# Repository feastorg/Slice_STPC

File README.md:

# Slice STPC

## Introduction

Stepper motor controller Slice for BREADS-compatible systems.
This Slice is a carrier board for the [Stepper_card](https://github.com/IanVDS/stepper_card) board. It can carry up to four stepper cards, each with a DRV8825 stepper driver with microstepping and SPI pins for encoder reading.

## Usage

[Explain how to use the project. Include examples and screenshots if applicable.]

## Documentation

Please refer to the [docs](/docs) for more info.

---

<div align="center">
  
</div>

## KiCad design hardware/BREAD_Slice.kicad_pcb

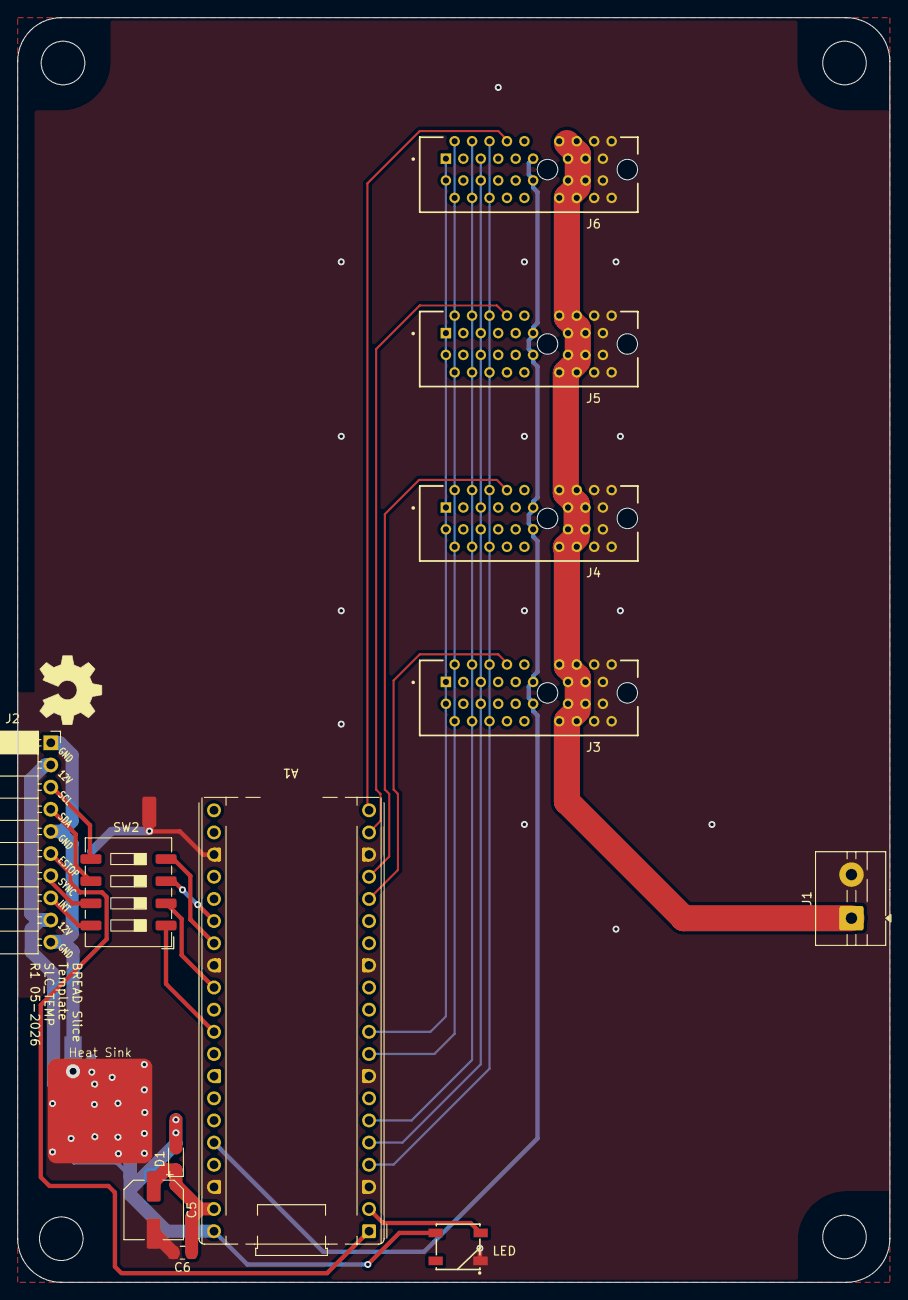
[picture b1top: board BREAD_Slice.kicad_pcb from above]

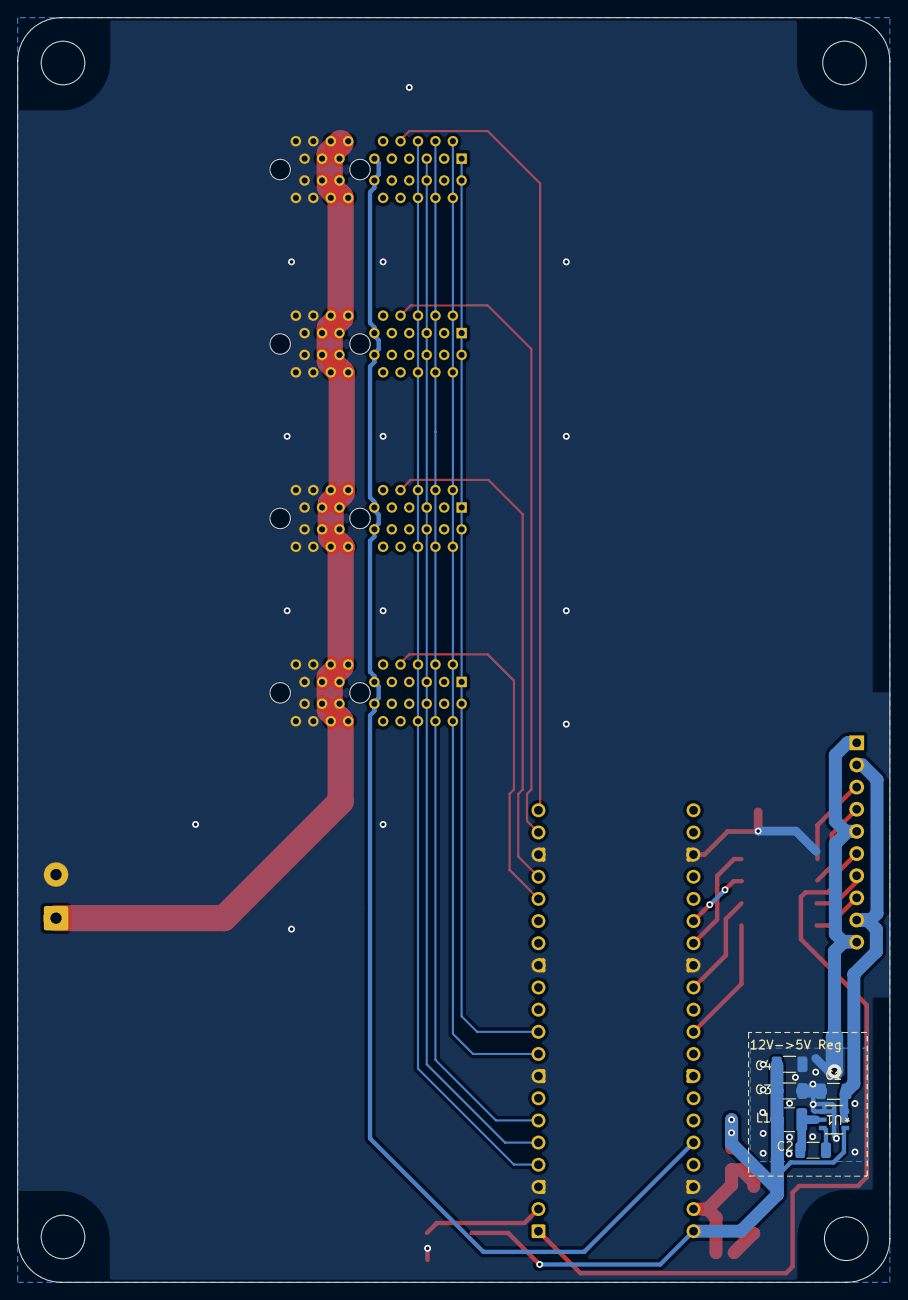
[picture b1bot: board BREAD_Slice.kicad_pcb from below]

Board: 4 copper layers, 100.0 x 145.0 mm, 25 parts (7 on the bottom side), 37 nets.

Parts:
A1: RaspberryPi_Pico; RaspberryPi_Pico_THT
C1: 10u; C_1206_3216Metric
C2: 100nF; C_1206_3216Metric
C3, C4: 22uF; C_1206_3216Metric
C5: 47u 25V; CP_Elec_6.3x7.7
C6: 0.1u; C_0805_2012Metric_Pad1.18x1.45mm_HandSolder
D1: BAT54WS-7-F; D_SOD-323_HandSoldering
D2: WS2812B_5050; WS2812-5050-4PIN
H1, H2, H3, H4: MountingHole; MountingHole_5mm
HS1: Heatsink_Pad; Thermal_Pad
J1: Screw_Terminal_01x02; TerminalBlock_MaiXu_MX126-5.0-02P_1x02_P5.00mm
J2: Conn_01x10_Socket; PinSocket_1x10_P2.54mm_Horizontal
J3, J4, J5, J6: PCIE-036-02-X-D-TH; SAMTEC_PCIE-036-02-X-D-TH
L1: 4.7uH; L_1210_3225Metric
NT1: NetTie_2; NetTie-2_SMD_Pad2.0mm
Ref**: Val**; OSHW_Logo_8mm
SW2: SW_DIP_x04; SW_DIP_SPSTx04_Slide_9.78x12.34mm_W8.61mm_P2.54mm
U1: AP63205; SOIC_05WU-7_DIO

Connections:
+3V3: A1.36 (3V3), J3.A11, J3.B11, J4.A11, J4.B11, J5.A11, J5.B11, J6.A11, J6.B11
+5V: A1.40 (VBUS), C3.2, C4.2, D1.2 (A), D2.1 (VDD), L1.2, U1.1 (FB)
+12V: C1.2, J2.2, J2.9, U1.2 (EN), U1.3 (VIN)
/CIPO: A1.6 (GPIO4), J3.A4, J3.B4, J4.A4, J4.B4, J5.A4, J5.B4, J6.A4, J6.B4
/COPI: A1.5 (GPIO3), J3.A5, J3.B5, J4.A5, J4.B5, J5.A5, J5.B5, J6.A5, J6.B5
/CS0: A1.25 (GPIO19), J3.A3
/CS1: A1.24 (GPIO18), J4.A3
/CS2: A1.22 (GPIO17), J5.A3
/CS3: A1.21 (GPIO16), J6.A3
/DIR0: A1.16 (GPIO12), J3.A8
/DIR1: A1.17 (GPIO13), J4.A8
/DIR2: A1.19 (GPIO14), J5.A8
/DIR3: A1.20 (GPIO15), J6.A8
/SCLK: A1.4 (GPIO2), J3.A6, J3.B6, J4.A6, J4.B6, J5.A6, J5.B6, J6.A6, J6.B6
/STEP0: A1.15 (GPIO11), J3.A7
/STEP1: A1.14 (GPIO10), J4.A7
/STEP2: A1.12 (GPIO9), J5.A7
/STEP3: A1.11 (GPIO8), J6.A7
/Stepper_card/SCL: A1.10 (GPIO7), J3.A1, J3.B1, J4.A1, J4.B1, J5.A1, J5.B1, J6.A1, J6.B1
/Stepper_card/SDA: A1.9 (GPIO6), J3.A2, J3.B2, J4.A2, J4.B2, J5.A2, J5.B2, J6.A2, J6.B2
/nFAULT: A1.32 (GPIO27_ADC1), J3.B8, J4.B8, J5.B8, J6.B8
/slice_template/ESTOP: A1.1 (GPIO0), J2.6
/slice_template/I2C0_CLK/GPIO21: A1.27 (GPIO21), SW2.4
/slice_template/I2C0_SDA/GPIO20: A1.26 (GPIO20), SW2.3
/slice_template/I2C_CLK: J2.3, SW2.5
/slice_template/I2C_DAT: J2.4, SW2.6
/slice_template/INT: J2.8, SW2.8
/slice_template/INT/CAN_{CS}: A1.31 (GPIO26_ADC0), SW2.1
/slice_template/LED: A1.2 (GPIO1), D2.4 (DIN)
/slice_template/SYNC: J2.7, SW2.7
/slice_template/SYNC/CAN_{INT}: A1.29 (GPIO22), SW2.2
/slice_template/VSYS: A1.39 (VSYS), C5.1, C6.1, D1.1 (K)
GND: A1.3 (GND), A1.8 (GND), A1.13 (GND), A1.18 (GND), A1.23 (GND), A1.28 (GND), A1.38 (GND), C1.1, C3.1, C4.1, C5.2, C6.2, D2.3 (VSS), HS1.1, J1.2, J3.A16, J3.A17, J3.A18, J3.B16, J3.B17, J3.B18, J4.A16, J4.A17, J4.A18, J4.B16, J4.B17, J4.B18, J5.A16, J5.A17, J5.A18, J5.B16, J5.B17, J5.B18, J6.A16, J6.A17, J6.A18, J6.B16, J6.B17, J6.B18, NT1.1, U1.4 (GND)
GNDPWR: J2.1, J2.5, J2.10, NT1.2
unnamed: C2.2, U1.6 (BST)
unnamed: C2.1, L1.1, U1.5 (SW)
VM: J1.1, J3.A12, J3.A13, J3.A14, J3.A15, J3.B12, J3.B13, J3.B14, J3.B15, J4.A12, J4.A13, J4.A14, J4.A15, J4.B12, J4.B13, J4.B14, J4.B15, J5.A12, J5.A13, J5.A14, J5.A15, J5.B12, J5.B13, J5.B14, J5.B15, J6.A12, J6.A13, J6.A14, J6.A15, J6.B12, J6.B13, J6.B14, J6.B15

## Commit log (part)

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2026-05-20 did schematic
2026-05-21 more routing
2026-05-22 finished initial routing
2026-05-22 added nFAULT line
2026-05-22 changed todo
2026-05-24 Fix pipeline and customize from template to STPC
    - Fix workflow org case: FEASTorg → feastorg (caused startup_failure)
    - Update all config/docs from TEMP_NANO_S2L-r2 template to STPC
    - Add root TODO.md with pipeline status and board dev tasks
2026-05-24 Update TODO with CI results
2026-05-24 Standardize TODO.md with Pass 1/Pass 2 structure
2026-06-11 Add slice.yaml manifest
